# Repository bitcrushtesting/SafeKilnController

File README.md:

<!--
SPDX-FileCopyrightText: 2026 Bitcrush Testing
SPDX-License-Identifier: GPL-3.0-or-later
-->

# Safe Kiln Controller

An open-source PID controller for electric ceramic and glass kilns, built on the
**ESP32-S3** with **ESP-IDF**.

- **Simple local display**: a 128×64 OLED showing current and target temperature at a glance, plus state, segment progress and rate of rise.
- **Web interface**: served by the device itself. Live dashboard, charts of the logged data, power and energy, and the firing programs the firmware carries. **Observation only**: nothing reachable over the network can start a firing, heat the kiln or change its configuration. Those are done at the kiln.
- **PID with automatic tuning**: relay (Åström–Hägglund) autotune on the real kiln; no manual gain hunting.
- **Firing profiles are compiled in**: the device ships with its curves and nothing edits them, not over the network and not at the kiln. That removes every authoring path and the attack surface each one carries, and it has a real cost: a curve of your own means building a firmware that carries it.
- **Safety first**: thermal runaway, thermocouple failure, shorted-SSR, over-temperature and door-interlock detection, with a safety supervisor that has sole authority over a heat-enable line that decays unless actively refreshed.
- **Current monitoring**: a current transformer turns relay and element failures from slow thermal inferences into fast electrical facts, with the thermal rules retained as an independent backstop.
- **Self-contained**: no SD card, no external database, no account, no filesystem. Logs live in a circular partition on internal flash and programs in a fixed-slot one, each built so a power cut cannot tear a record; web assets are embedded in the firmware. The device makes **one** outbound connection, a daily check for a firmware update that carries nothing about the device and can be turned off at the display.
- **Designed for testability**: all decision logic is hardware-free C++ that runs on a development host against a simulated kiln.

The dashboard mid-firing. Everything on it is read from the device: the `RUN`
and `HEAT` badges, the segment progress, the logged curve. There is no button
here that changes what the kiln is doing, because there is no route behind one
(`SWR-WEB-26`), which is why both notices at the foot of the page say so
plainly.

No kiln was involved. That is the development harness of
[`host/webhost`](firmware/controller/host/webhost) running the real firmware
logic against a simulated one, and it is two commands if you want to click
around yourself:

```sh
cmake -B build-webhost -S firmware/controller/host/webhost && cmake --build build-webhost
./build-webhost/webhost --accel 60 --fire "Bisque cone 06"   # then open http://127.0.0.1:8080
```

`--fire` exists because of the read-only interface: a firing cannot be started
from the browser, so the harness starts one of the built-in examples
(`SWR-PRG-09`) through the same call the local display makes.

## Status

**In development, and not ready to fire a kiln.** The control, safety, storage,
web and interface logic is written and tested. The hardware adapters are
written and **have never been run against a board**. Two things block a
release: the field update path is specified and unbuilt, and local control,
which is now the only control, has never been operated by a person.

433 host tests on the controller and 81 on the independent safety supervisor,
all green plain and under AddressSanitizer and UBSan. `clang-tidy` is clean on
host and target with no suppressions baseline, MC/DC over the supervisor's trip
logic is 100 % against an 80 % floor, the `esp32s3` image builds with zero
warnings at 246 kB (88 % of the OTA slot free), and QEMU boots that image and
fires it. The hardware configuration, which that one compiles out, builds at
908 kB with the browser interface gzipped into it and 56 % of the slot free.

The controller is C++20; the supervisor is C++17, which is the standard
MISRA C++:2023 is written against. What is done, what is not, and what blocks
a release is [`tasklist.md`](tasklist.md), which is kept current and is the
only place that count lives.

You can watch a complete firing, and break it in a dozen ways, without any
hardware at all, see [`docs/simulation.md`](docs/simulation.md):

```sh
tools/run-qemu.sh          # the firmware on an emulated ESP32-S3, kiln simulated
```

or run the logic tests directly:

```sh
cmake -B build-host -S firmware/controller/test/host && cmake --build build-host
ctest --test-dir build-host
```

CI runs eleven jobs: the layering and licence checks, both host suites plain
and under AddressSanitizer and UBSan, a coverage gate, `clang-tidy` on host and
on target, StrictDoc over the requirements, the `esp32s3` build with a size
report and a generated bill of materials, the supervisor suites with MC/DC, the
unit design document with documentation warnings as errors, and a QEMU job that
boots the real image and asserts that the simulated kiln passes 100 degC
without latching a fault. Tagging `v*` builds a release.

## Putting a unit into production

Two tools, in this order, because the order is not interchangeable:

```sh
tools/prod-data.py flash --serial SK1-2026-000042   # identity, a plain write
tools/secure-boot.py provision --key keys/prod.pem  # dry run; add --commit
```

The production data block first, while the device is still freely writable.
Then signing, flashing and lockdown.

The two differ in what they do by default, and the difference is the point.
`prod-data.py` writes unless told `--dry-run`, because its write is a plain
flash write that a reflash undoes. `secure-boot.py` does *nothing* unless told
`--commit`, because most of what it does cannot be undone at all. Both carry a
`--self-test` that needs neither a board nor ESP-IDF.

**`secure-boot.py` burns eFuses, and three of its four steps cannot be undone.**
It refuses to touch a board until its pre-flight passes, demands a differently
worded confirmation for each irreversible step, and sequences them so the device
is left bootable at every point. Read the header of
[`firmware/controller/sdkconfig.secure`](firmware/controller/sdkconfig.secure) before the first run;
the short version is that **losing the signing key means the unit can never run
new firmware again**, and that secure boot stops hostile code running but does
nothing about secrets being read off the flash (`SRR-05`).

### Releasing an update

A third tool, for the other end of the lifecycle. The device fetches one signed
static manifest per channel and verifies it against a key compiled into its own
firmware (`SWR-UPD-09` to `SWR-UPD-16`), and this builds that manifest:

```sh
tools/update-manifest.py keygen --key keys/manifest.pem          # once, then keep it offline
tools/update-manifest.py pubkey --key keys/manifest.pem \
    --header firmware/controller/main/update_pubkey.h            # the half that ships
tools/update-manifest.py sign   --key keys/manifest.pem \
    --image build-esp32s3/safekiln.bin --version 1.4.2 \
    --security --advisory advisories/2026-002.html
tools/update-manifest.py verify --manifest dist/update/stable.json \
    --pubkey keys/manifest.pub.pem --image build-esp32s3/safekiln.bin \
    --running-version 1.4.1
```

The **bill of materials** is generated rather than written
([`tools/sbom.py`](tools/sbom.py), `SWR-NFR-28`): the component list comes from
the build's own `project_description.json`, so it names what was actually
linked, and each licence is scanned from that component's own
`SPDX-License-Identifier` tags, with anything untagged reported as
`NOASSERTION` rather than given a plausible default. CycloneDX 1.6 by default,
SPDX 2.3 with `--format spdx`, both published with every release:

```sh
tools/sbom.py --build-dir firmware/controller/build \
    --image firmware/controller/build/safekiln.bin --format both --strict
```

It has to run where `$IDF_PATH` is, which in CI means inside the IDF container
rather than a step afterwards, because a licence cannot be scanned from a tree
that is not there. The question it exists to answer is "an advisory landed this
morning against mbedTLS 3.6.0, did we ship it", and that cannot be answered
after the fact.

**The manifest key is not the secure boot key, and the tool refuses to let it
be** (`SRR-12`). The secure boot key decides what a provisioned board will
*boot* and its digest is burnt into eFuses, so it can never be rotated; this one
decides what a board will be *offered* and is used on every release. `sign` also
refuses an image with no Secure Boot V2 signature, an image whose chip id is not
this target, a version carrying build metadata, and a security release with no
advisory, because each of those produces a manifest that every device must
reject after downloading it.

It deliberately does not burn `DIS_DOWNLOAD_MODE`. Serial download is
`SWR-UPD-14`'s recovery path, for a unit whose update service is unreachable,
whose new image will not confirm itself, or which has to be downgraded; closing
it as well would make such a unit permanently unfixable.

| Document | Contents |
|---|---|
| [`docs/v-model-process.md`](docs/v-model-process.md) | The development process: the V-model levels, which document holds each, the relations between them, and an honest record of which levels exist and which do not. |
| [`docs/01_user_req.sdoc`](docs/01_user_req.sdoc) | User requirements: the target markets (the European Union), the regulatory framework that follows from them with instrument numbers and editions, the user needs with their acceptance criteria, and the project constraints. |
| [`docs/02_system_req.sdoc`](docs/02_system_req.sdoc) | System requirements: the hardware interface, the four safety requirements that hardware discharges, and the assumptions about the environment the system is placed in. |
| [`docs/03_software_req.sdoc`](docs/03_software_req.sdoc) | Software requirements: the functional, safety, non-functional and testability requirements, each with an identifier and a verification method. |
| [`docs/04_software_arch.sdoc`](docs/04_software_arch.sdoc) | Software architecture: the 22 decisions the design rests on, each with the requirement that drove it and the cost it carries. |
| [`docs/safety.sdoc`](docs/safety.sdoc) | Hazards, safety goals and residual risks, each with an identifier, and the chain between them as checked relations: which hazards a goal mitigates, which requirements realise it, and which risk its layers leave. |
| [`docs/safety.md`](docs/safety.md) | Safety concept: the system boundary, the layered protection concept and the independence claimed between layers, detection coverage and timing, the reaction and recovery sequence, and the obligations on the installer and on anyone changing the design. |
| [`docs/security.sdoc`](docs/security.sdoc) | Assets, adversaries, threats, security goals, residual risks and open questions, each with an identifier, and the chain between them as checked relations: which asset a threat is aimed at, which safety hazard it reaches, which goal answers it, and what each goal's implementation status actually is. |
| [`docs/security.md`](docs/security.md) | Security concept: scope, the attack surface and trust boundaries, the physical boundary and why the supervisor's debug port is deliberately open, the update path and why it points outwards, why a security compromise here is a safety event, what the implementation already gets right, the obligations on the owner and on whoever implements the HTTP transport, the verification status, and an inventory of what the Cyber Resilience Act still requires. |
| [`SECURITY.md`](SECURITY.md) | The security policy: where to report a vulnerability and what happens then, the single point of contact and the reporting obligations behind it, the supported versions and the support period, how a fix reaches a device, and what is already documented as a residual risk so a report need not restate it. |
| [`docs/architecture.md`](docs/architecture.md) | Architecture prose: component decomposition, task and timing design, control and safety algorithms, persistence and flash-endurance design, REST API, and the build and test architecture. |
| [`docs/test-concept.md`](docs/test-concept.md) | How the product is verified: unit, integration, system and hardware-in-the-loop, what each level can and cannot prove, the HIL fixture design, and an honest status against every testability requirement. |
| [`docs/safety-supervisor.md`](docs/safety-supervisor.md) | The independent safety supervisor (`SWA-22`): a second microcontroller holding the absolute over-temperature, thermocouple-fault and lid trips, what moves and what stays, the link, the failure modes, and the questions still open. |
| [`docs/coding-standard.md`](docs/coding-standard.md) | The coding standard: which safety standards actually reach the source code and what each asks for, the language subset and the flags that enforce it, why the supervisor contains no floating point, how a deviation is recorded, and what is not met yet. |
| [`docs/simulation.md`](docs/simulation.md) | Running the firmware against a simulated kiln, on the host and under QEMU, including fault injection. |
| [`tasklist.md`](tasklist.md) | Outstanding work, by priority. |

Start with [`docs/03_software_req.sdoc`](docs/03_software_req.sdoc); the architecture
document cites it throughout.

## Repository layout

```
docs/                  requirements, architecture, safety and security
firmware/controller/   the ESP-IDF application
firmware/supervisor/   the independent safety supervisor, STM32G031
web/                   the browser interface, served by the device
tools/                 release, provisioning, analysis and document generation
fixture/               the bed-of-nails test fixture
hardware/              schematic, PCB, pin map
housing/               enclosure
```

## Scope

Safe Kiln Controller supports **single-phase kilns only**. A three-phase kiln can be
monitored on one representative phase, but a fault confined to one of the other
two would be caught only by the thermal rules, slowly, and the power and energy
figures would cover a third of the load. Neither is a safe basis for firing a
three-phase kiln, so it is out of scope rather than partially supported.

## Hardware at a glance

| Part | Choice |
|---|---|
| MCU | ESP32-S3, ≥ 8 MB flash, no PSRAM required |
| Temperature | MAX31856 front ends, type-K. The controller reads chamber and enclosure; the **supervisor reads its own chamber couples on its own SPI buses**, so neither processor depends on the other for a temperature |
| Display | 128×64 monochrome OLED, I²C |
| Input | Rotary encoder with push button |
| Output | Zero-cross SSR in series with a 2-pole safety relay |
| Supply | **Single phase only.** One current transformer on the heater conductor |
| Door interlock | Optional normally-closed switch, stops the heater immediately when the door opens |
| Connectivity | WiFi station only. **No access point:** the network is selected and its passphrase typed at the display, so setting it up needs somebody at the kiln. Reachable at `kiln.local` over mDNS, and by IP, which the display shows |

Details and rationale are in
[requirements §6](docs/03_software_req.sdoc).

### Wiring

The relay breaks both L and N, so a reversed plug cannot leave the elements
live. The SSR switches L, and the current transformer sits downstream of both.
The terminal-by-terminal wiring tables, the parts and the two-part wall-mount
housing are in [`hardware/enclosure/README.md`](hardware/enclosure/README.md#wiring).

The full board schematic is exported as
[`docs/hardware/safekiln-schematic.pdf`](docs/hardware/safekiln-schematic.pdf);
the source is [`hardware/safekiln.kicad_sch`](hardware/safekiln.kicad_sch).

## Credit

Functionally inspired by [**PIDKiln**](https://github.com/Saur0o0n/PIDKiln) by
Adrian Siemieniak, which showed that a low-cost ESP32 can run a real kiln well.
Safe Kiln Controller borrows its ideas, segment-based programs, dual local/web control,
on-device storage, a redundant SSR + contactor output stage, and rebuilds them
on ESP-IDF with a host-testable core and automatic PID tuning. No PIDKiln source
code is used

## Safety

Safe Kiln Controller is **not** a safety-certified device. A kiln is a multi-kilowatt mains
heater reaching temperatures at which its own wiring and the surrounding building
are at risk.

Mains wiring must be carried out by a competent person in accordance with local regulation.

The hazards, the layered protection concept and the risk that remains are
set out in [`docs/safety.md`](docs/safety.md); the requirements it derives from
are [requirements §5](docs/03_software_req.sdoc).

Safe Kiln Controller is designed for a **trusted local network** and must not be exposed
to the internet. The threat model, the controls and what is still only specified are in [`docs/security.md`](docs/security.md).

## License

GPL-3.0-or-later. See [`LICENSE`](LICENSE).

    Copyright (C) 2026 Bitcrush Testing

    This program is free software: you can redistribute it and/or modify it
    under the terms of the GNU General Public License as published by the Free
    Software Foundation, either version 3 of the License, or (at your option)
    any later version.

    This program is distributed in the hope that it will be useful, but WITHOUT
    ANY WARRANTY; without even the implied warranty of MERCHANTABILITY or
    FITNESS FOR A PARTICULAR PURPOSE.  See the GNU General Public License for
    more details.

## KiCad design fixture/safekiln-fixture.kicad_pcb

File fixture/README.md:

<!--
SPDX-FileCopyrightText: 2026 Bitcrush Testing
SPDX-License-Identifier: GPL-3.0-or-later
-->

# Bed-of-nails fixture

The hardware-in-the-loop fixture for the controller board, built from the board
itself by [pinside](https://github.com/bitcrushtesting/pinside). This is the
fixture `docs/test-concept.md` wants and that the M4 and M4b milestones need:
`safety.md` §10 still lists the central claim of the design, that the contactor
releases when the safety task stops, as **not yet performed**, and nothing in
this repository can perform it without a jig.

## What is here

| | |
|---|---|
| `kilncontrol-fixture.json` | the fixture definition. **This is the source**; everything else is generated from it |
| `pinside-baseline.json` | findings on the DUT that have been looked at and accepted, with the reason for each |
| `board/` | a KiCad project for the fixture board, generated |
| `firmware/` | firmware for the fixture's controller, generated |

`board/` and `firmware/` are generated verbatim and are regenerated, not edited.
pinside derives footprint UUIDs from the config rather than randomising them, so
an unchanged config produces a byte-identical project and the diff of a real
change is only the change.

## Regenerating

```sh
pip install pinside                       # or run from a checkout, see its README
pinside check    hardware/safekiln.kicad_pcb --baseline fixture/pinside-baseline.json
pinside project  fixture/kilncontrol-fixture.json --out fixture/board
pinside generate fixture/kilncontrol-fixture.json --out fixture/firmware
bash fixture/firmware/test/run.sh         # 128 host checks, no hardware needed
```

`project` needs KiCad installed, because a schematic embeds a copy of every
symbol it places. `check` and `generate` do not. The board file is only ever
read; pinside never writes KiCad sources.

## Two decisions worth knowing

**The probe is a Mill-Max 0906, not the default 0985.** With the 0985's 2.54 mm
minimum pitch, eight probe pairs on this board collide: TP2-TP3, TP6-TP9,
TP7-TP8, TP15-TP16, TP19-TP20, TP20-TP22, TP21-TP34 and TP32-TP36 all sit at
exactly 2.50 mm, because the test points are on a 2.5 mm grid and the receptacle
body is wider than that. The 0906's 1.91 mm pitch clears all eight, and its
lower 0.55 N force halves the plate load as a side effect. Its dimensions are
pinside's reading of the Mill-Max catalogue and **nobody has checked them
against a supplier drawing**; do that before ordering.

**The fixture carries the RP2350 itself rather than a Pico 2 module.** 28 test
points need more channels than a Pico 2's 26 header GPIO, and the first attempt
failed on exactly that: `COIL_PERMIT` and `SUPERVISOR_RESET` had nowhere to go,
with one GPIO spare. Those two are the permit line and the supervisor's reset,
which are the whole point of a safety fixture, so the carrier is `bare` with an
`rp2350b` (48 GPIO).

## What still blocks building it

**The board has no mounting holes, and that is two problems rather than one.**
`PS050` reports it as "the DUT can pivot or rock and contact becomes
intermittent", which is the mechanical half. The other half is quieter: on a
pinside fixture **the ground return goes through the grounded mounting holes**,
which is why `GND` is not a channel and why only 27 of the 28 test points get a
probe. pinside's own example board has its mounting holes on the `GND` net. With
no holes at all, the fixture's ground pour connects to the DUT through nothing,
and `PS031`, "only one ground test point", is the same problem seen from the
other side.

So before a fixture can be ordered the controller board needs **at least three
plated mounting holes on the GND net**, positioned so the probes fall inside
their span (`PS052` watches for that). Both findings are deliberately left out
of the baseline so they keep failing until that happens.

**Two analogue channels are placed but cannot be used.** `TC1_P` and `TC1_N` are
the thermocouple's millivolt inputs. The probes are placed so the pads are
reachable, and both are configured as observed inputs that the fixture **never
drives**: a GPIO asserting 3V3 into a thermocouple input can damage the front
end. Injecting a temperature, which is what a HIL suite actually wants, needs a
calibrated millivolt source the fixture does not have. `CURR_SENSE` is in the
same position and should become an ADC channel once the conditioning scale is
taken from the schematic; it is left as an observed input rather than having a
scale invented for it.

## The directions were reviewed, and the schematic is the authority

`pinside init` drafts a config and says to treat it as a draft. It defaulted
almost every signal to `open_drain` with `active_low`, which is a safe default
because `released` means not driving, but it is a default rather than an
analysis. The directions here were set by hand from the net names:

- **13 observed inputs**, every signal the DUT drives: `SSR1`, `HEAT_EN`,
  `PUMP_NODE`, `HEAT_EN_DC`, `COIL_DRV`, `COIL_PERMIT`, `ALARM`, `TC1_DRDY`,
  `TC1_FAULT`, `TC1_CS`, plus the three analogue ones above. A fixture that
  drove any of these would contend with the board.
- **6 driven**, the signals the DUT reads: `ENC_A`, `ENC_B`, `ENC_BTN`,
  `ESP32_EN`, `ESP32_IO0`, `SUPERVISOR_RESET`. Open-drain and active-low suits
  all six: each sits on a pull-up, and released means the fixture is holding the
  board in no particular state.

`TC1_CS` deserves its own note. The config declares an SPI peripheral in master
role, so the fixture *can* drive that bus, but chip select is left as an input
because the controller drives it in normal operation. Mastering the bus means
holding the DUT in reset through `ESP32_EN` first, and that interlock is not
configured here: it is a deliberate act, not a default.

These are a reading of the net names and of the firmware, not of the schematic.
**Check them against the schematic before power is applied to a real board**,
because the failure mode of a wrong direction is two drivers fighting.

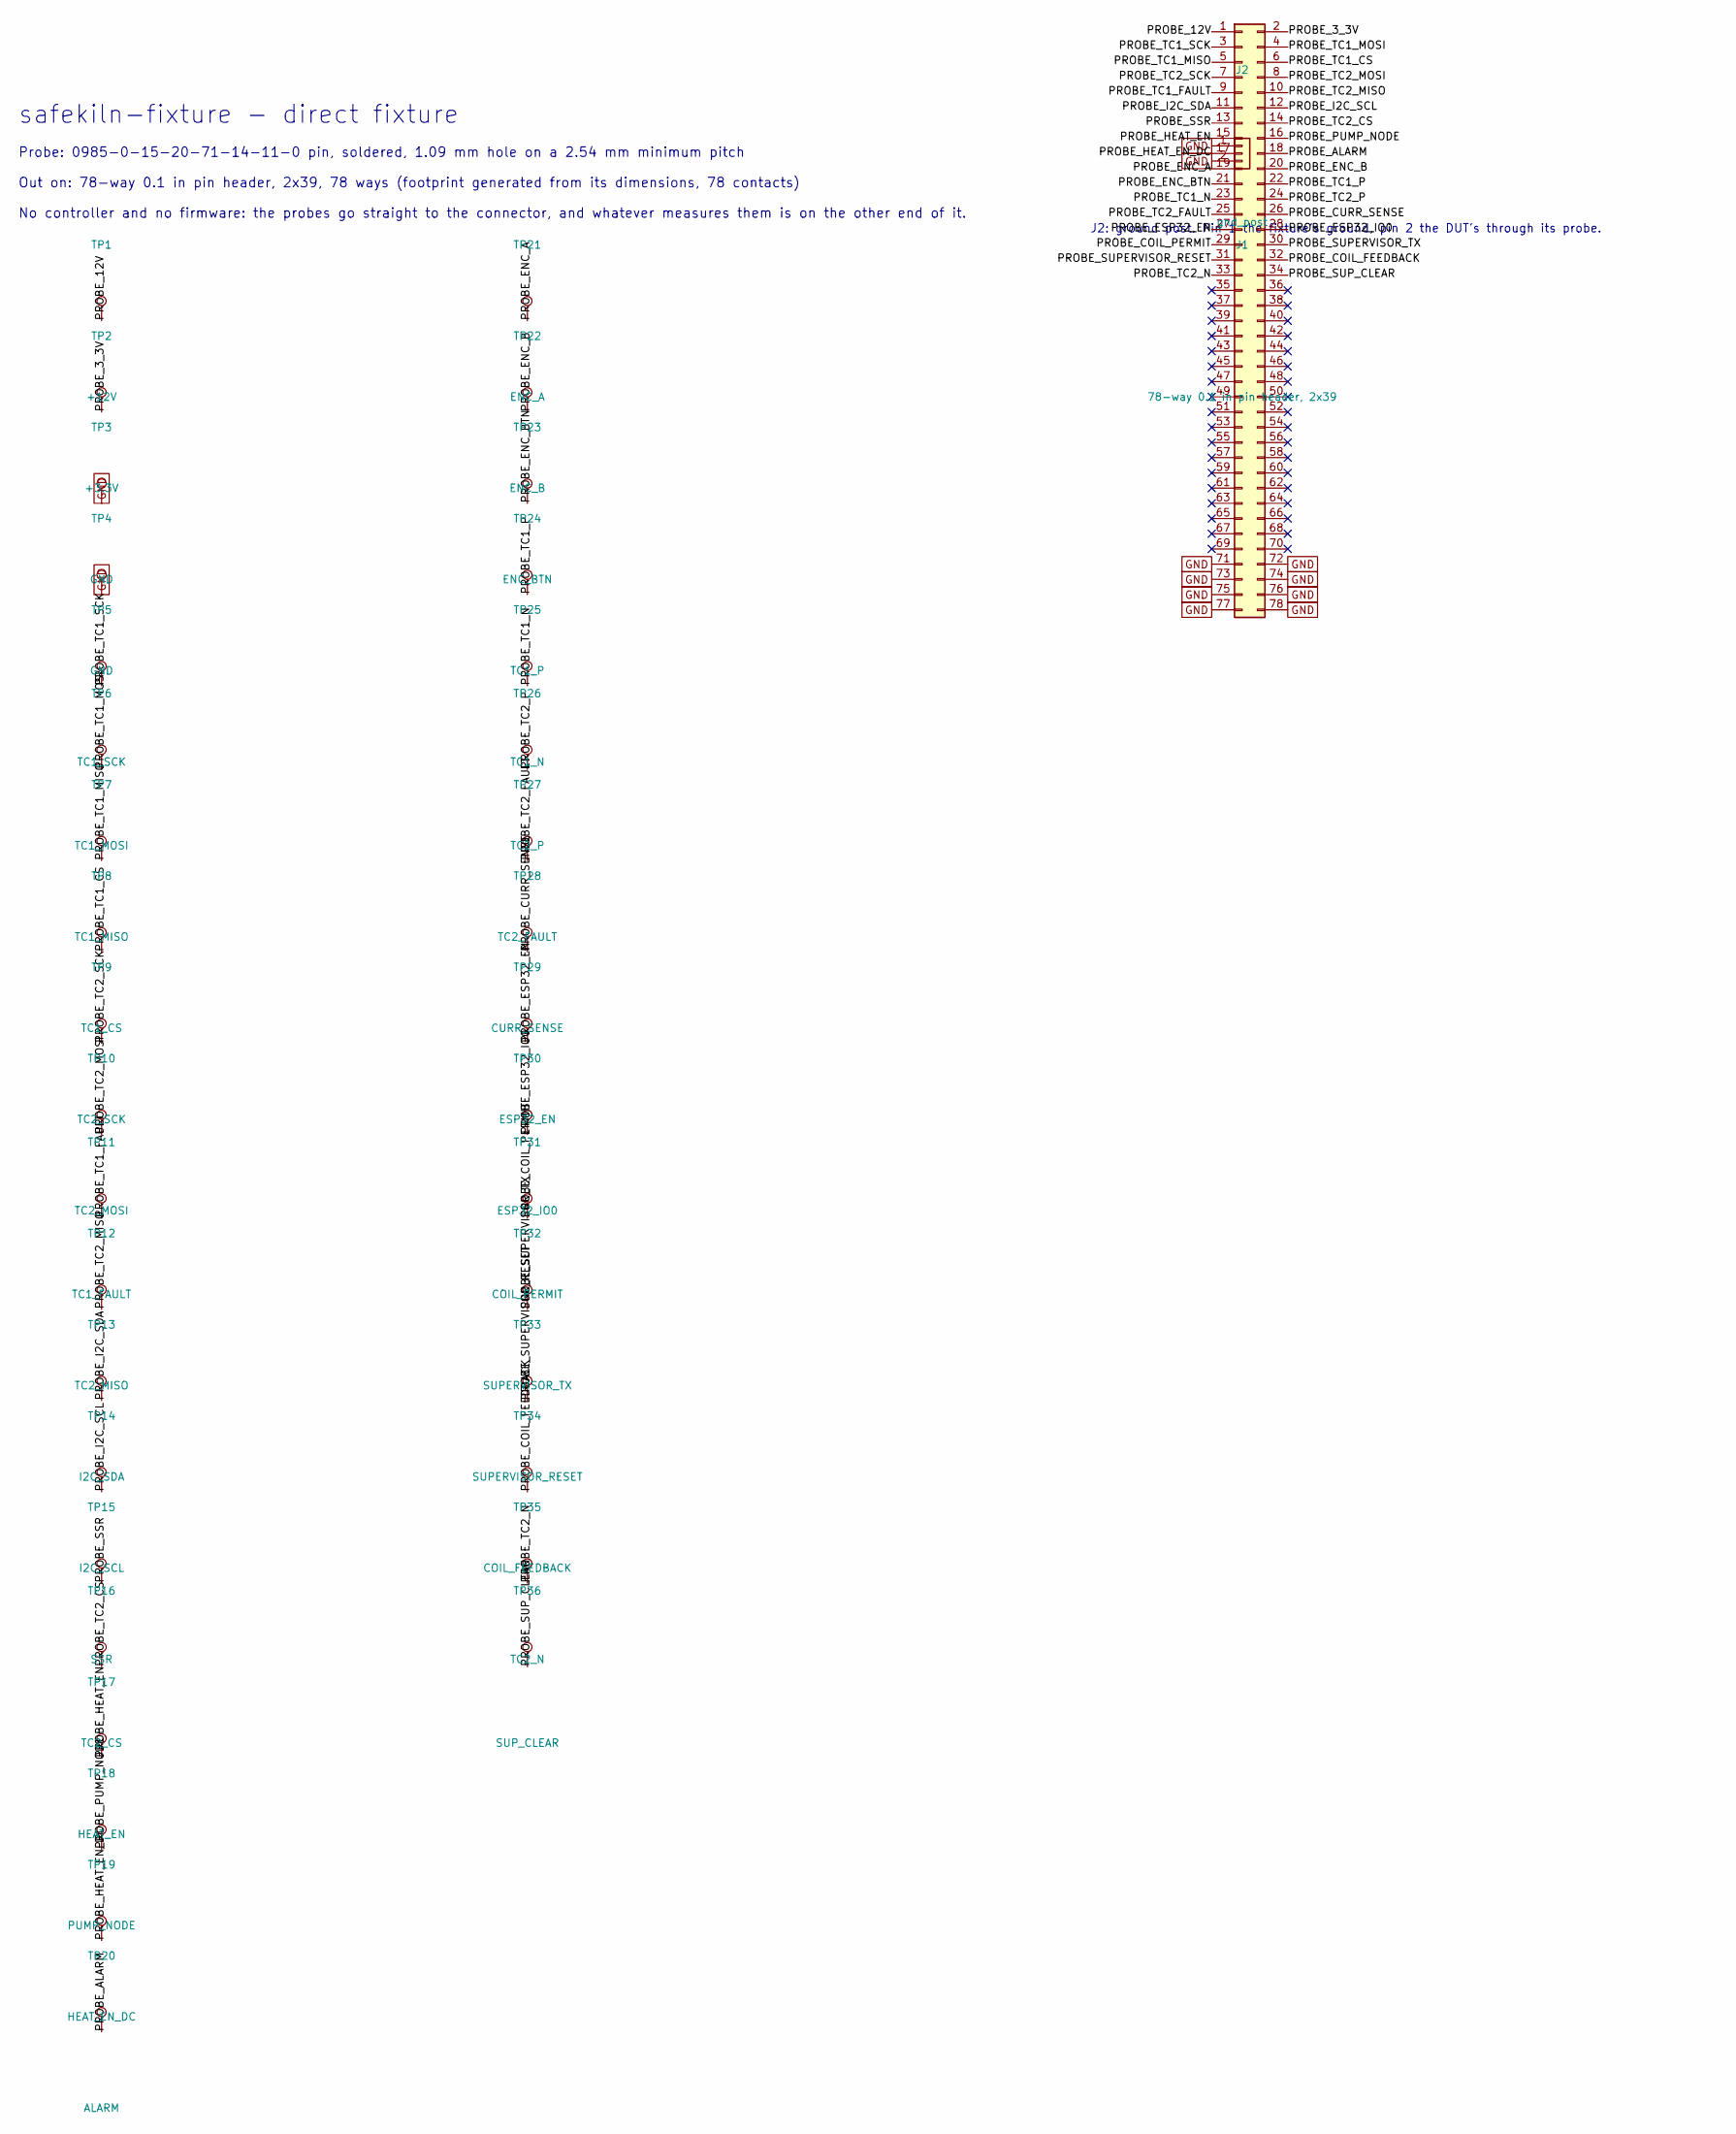
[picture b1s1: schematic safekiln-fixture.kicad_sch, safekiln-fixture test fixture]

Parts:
J1: 78-way 0.1 in pin header, 2x39; Connector_header_78
J2: gnd_post; Connector_gnd_post
TP1: +12V; PogoPin_millmax_0985
TP2: +3.3V; PogoPin_millmax_0985
TP3, TP4: GND; PogoPin_millmax_0985
TP5: TC1_SCK; PogoPin_millmax_0985
TP6: TC1_MOSI; PogoPin_millmax_0985
TP7: TC1_MISO; PogoPin_millmax_0985
TP8: TC1_CS; PogoPin_millmax_0985
TP9: TC2_SCK; PogoPin_millmax_0985
TP10: TC2_MOSI; PogoPin_millmax_0985
TP11: TC1_FAULT; PogoPin_millmax_0985
TP12: TC2_MISO; PogoPin_millmax_0985
TP13: I2C_SDA; PogoPin_millmax_0985
TP14: I2C_SCL; PogoPin_millmax_0985
TP15: SSR; PogoPin_millmax_0985
TP16: TC2_CS; PogoPin_millmax_0985
TP17: HEAT_EN; PogoPin_millmax_0985
TP18: PUMP_NODE; PogoPin_millmax_0985
TP19: HEAT_EN_DC; PogoPin_millmax_0985
TP20: ALARM; PogoPin_millmax_0985
TP21: ENC_A; PogoPin_millmax_0985
TP22: ENC_B; PogoPin_millmax_0985
TP23: ENC_BTN; PogoPin_millmax_0985
TP24: TC1_P; PogoPin_millmax_0985
TP25: TC1_N; PogoPin_millmax_0985
TP26: TC2_P; PogoPin_millmax_0985
TP27: TC2_FAULT; PogoPin_millmax_0985
TP28: CURR_SENSE; PogoPin_millmax_0985
TP29: ESP32_EN; PogoPin_millmax_0985
TP30: ESP32_IO0; PogoPin_millmax_0985
TP31: COIL_PERMIT; PogoPin_millmax_0985
TP32: SUPERVISOR_TX; PogoPin_millmax_0985
TP33: SUPERVISOR_RESET; PogoPin_millmax_0985
TP34: COIL_FEEDBACK; PogoPin_millmax_0985
TP35: TC2_N; PogoPin_millmax_0985
TP36: SUP_CLEAR; PogoPin_millmax_0985

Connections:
GND: J1.71, J1.72, J1.73, J1.74, J1.75, J1.76, J1.77, J1.78, J2.1, J2.2, TP3.1, TP4.1; also elsewhere on the board
PROBE_3_3V: J1.2, TP2.1
PROBE_12V: J1.1, TP1.1
PROBE_ALARM: J1.18, TP20.1
PROBE_COIL_FEEDBACK: J1.32, TP34.1
PROBE_COIL_PERMIT: J1.29, TP31.1
PROBE_CURR_SENSE: J1.26, TP28.1
PROBE_ENC_A: J1.19, TP21.1
PROBE_ENC_B: J1.20, TP22.1
PROBE_ENC_BTN: J1.21, TP23.1
PROBE_ESP32_EN: J1.27, TP29.1
PROBE_ESP32_IO0: J1.28, TP30.1
PROBE_HEAT_EN: J1.15, TP17.1
PROBE_HEAT_EN_DC: J1.17, TP19.1
PROBE_I2C_SCL: J1.12, TP14.1
PROBE_I2C_SDA: J1.11, TP13.1
PROBE_PUMP_NODE: J1.16, TP18.1
PROBE_SSR: J1.13, TP15.1
PROBE_SUPERVISOR_RESET: J1.31, TP33.1
PROBE_SUPERVISOR_TX: J1.30, TP32.1
PROBE_SUP_CLEAR: J1.34, TP36.1
PROBE_TC1_CS: J1.6, TP8.1
PROBE_TC1_FAULT: J1.9, TP11.1
PROBE_TC1_MISO: J1.5, TP7.1
PROBE_TC1_MOSI: J1.4, TP6.1
PROBE_TC1_N: J1.23, TP25.1
PROBE_TC1_P: J1.22, TP24.1
PROBE_TC1_SCK: J1.3, TP5.1
PROBE_TC2_CS: J1.14, TP16.1
PROBE_TC2_FAULT: J1.25, TP27.1
PROBE_TC2_MISO: J1.10, TP12.1
PROBE_TC2_MOSI: J1.8, TP10.1
PROBE_TC2_N: J1.33, TP35.1
PROBE_TC2_P: J1.24, TP26.1
PROBE_TC2_SCK: J1.7, TP9.1

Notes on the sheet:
safekiln-fixture - direct fixture
Probe: 0985-0-15-20-71-14-11-0 pin, soldered, 1.09 mm hole on a 2.54 mm minimum pitch
Out on: 78-way 0.1 in pin header, 2x39, 78 ways (footprint generated from its dimensions, 78 contacts)
No controller and no firmware: the probes go straight to the connector, and whatever measures them is on the other end of it.
J2: ground post. Pin 1 the fixture's ground, pin 2 the DUT's through its probe.

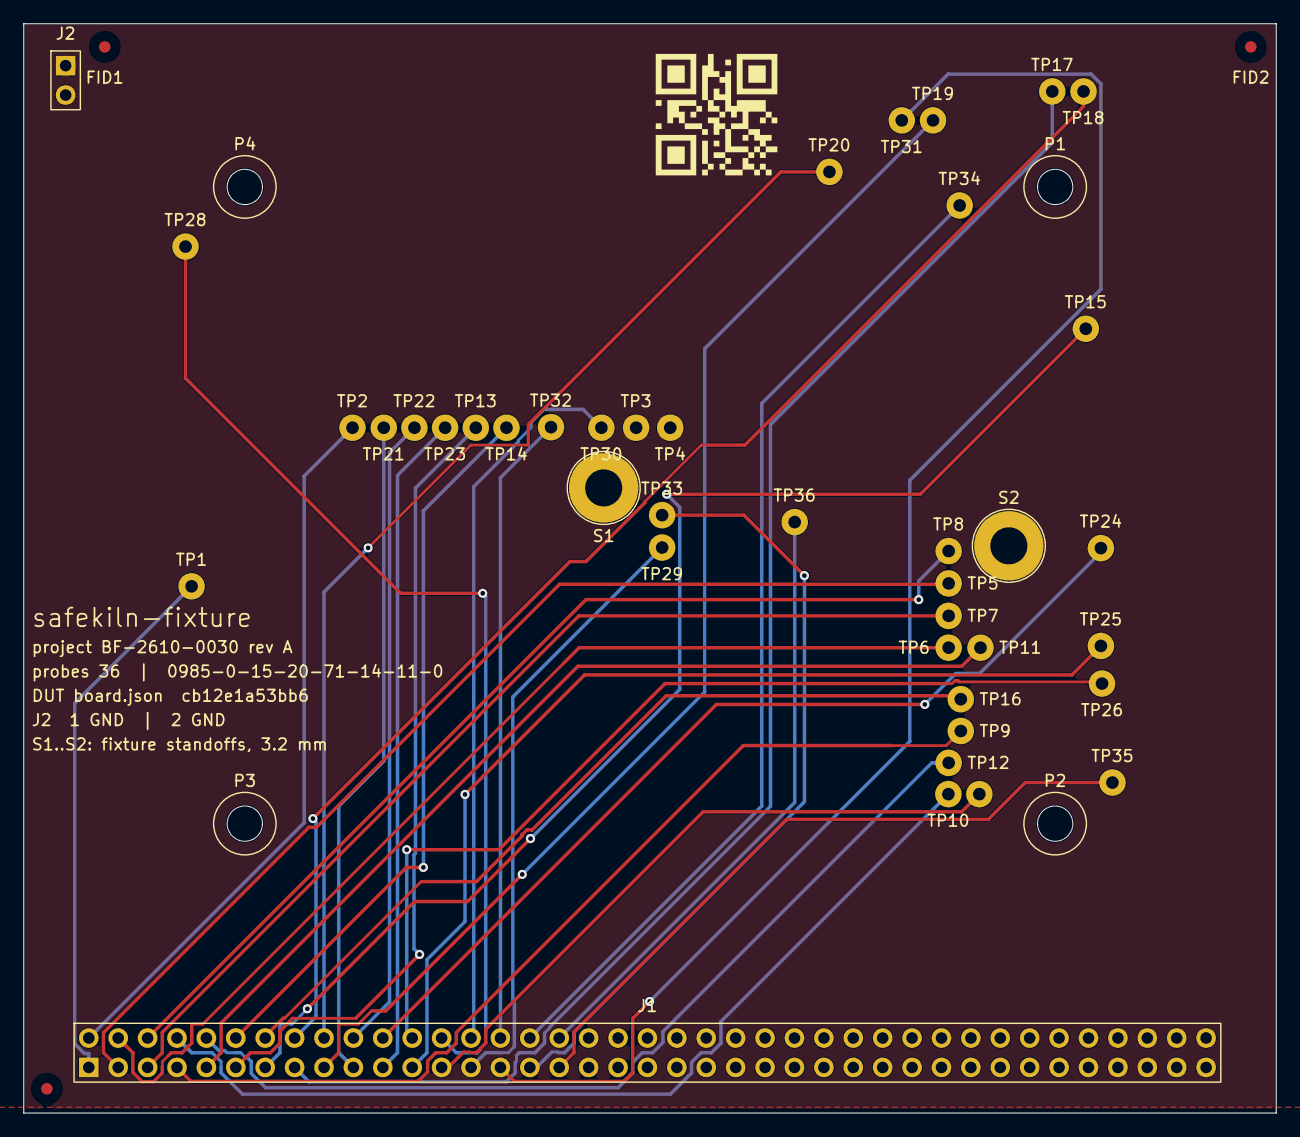
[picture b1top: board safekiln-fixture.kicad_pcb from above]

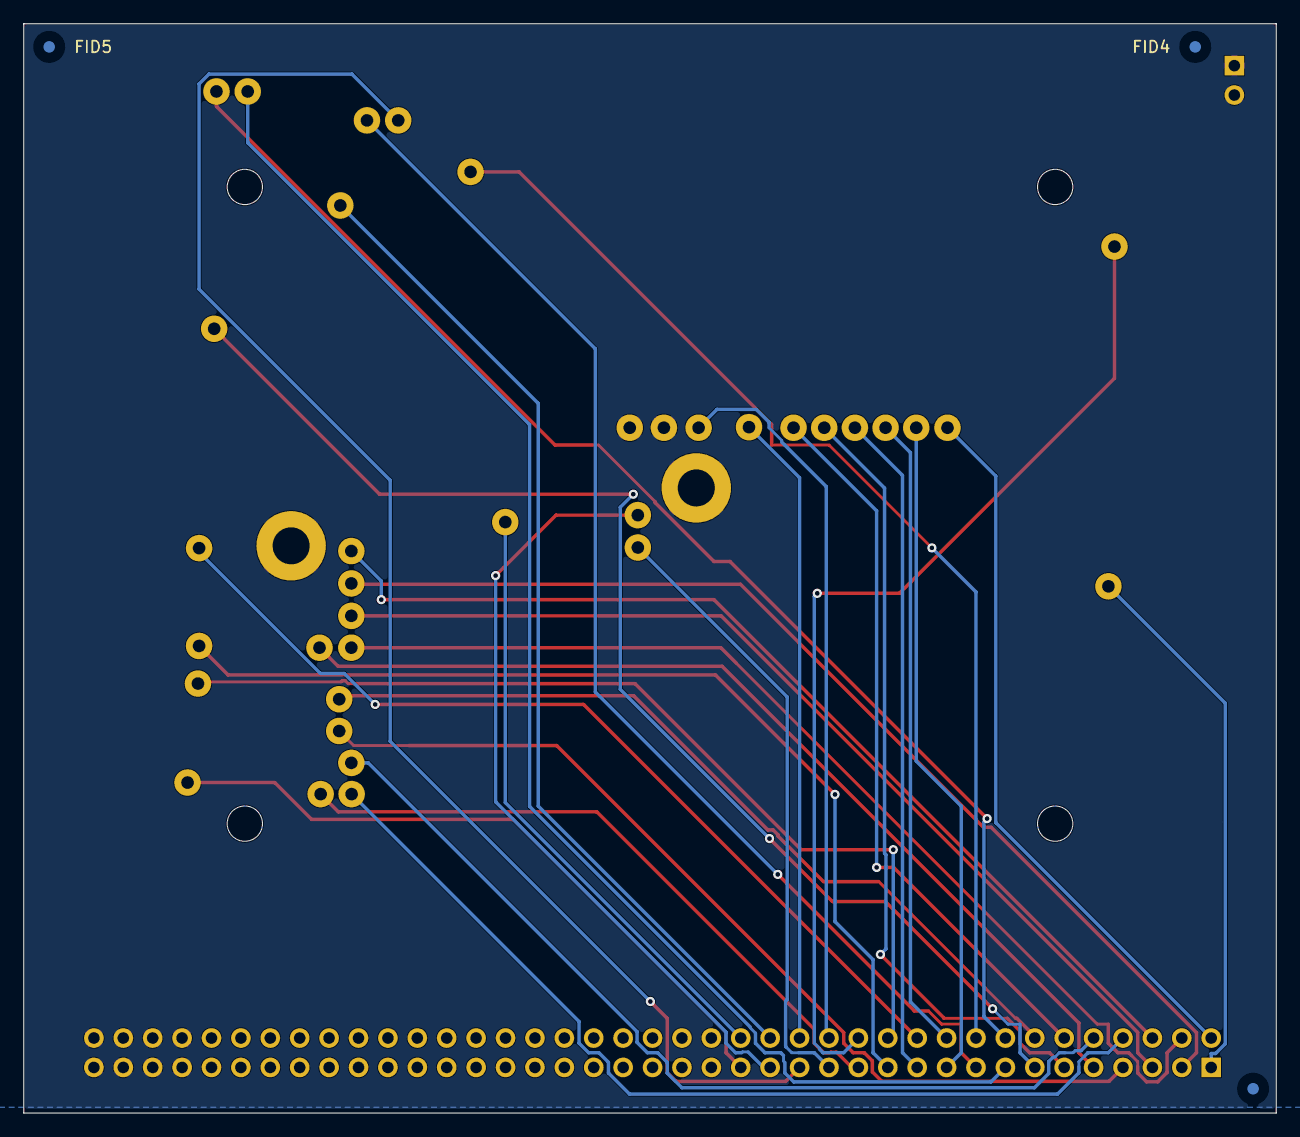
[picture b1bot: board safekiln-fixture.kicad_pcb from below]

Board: 2 copper layers, 108.2 x 94.1 mm, 50 parts (3 on the bottom side), 35 nets.

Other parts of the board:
FID1, FID2, FID3, FID4, FID5, FID6: Fiducial_1mm
P1, P2, P3, P4: 3mm pin; ClampPinHole_3.05mm
S1, S2: 3.2mm; MountingHole_3.2mm

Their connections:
GND: S1.1, S2.1; also elsewhere on the board
